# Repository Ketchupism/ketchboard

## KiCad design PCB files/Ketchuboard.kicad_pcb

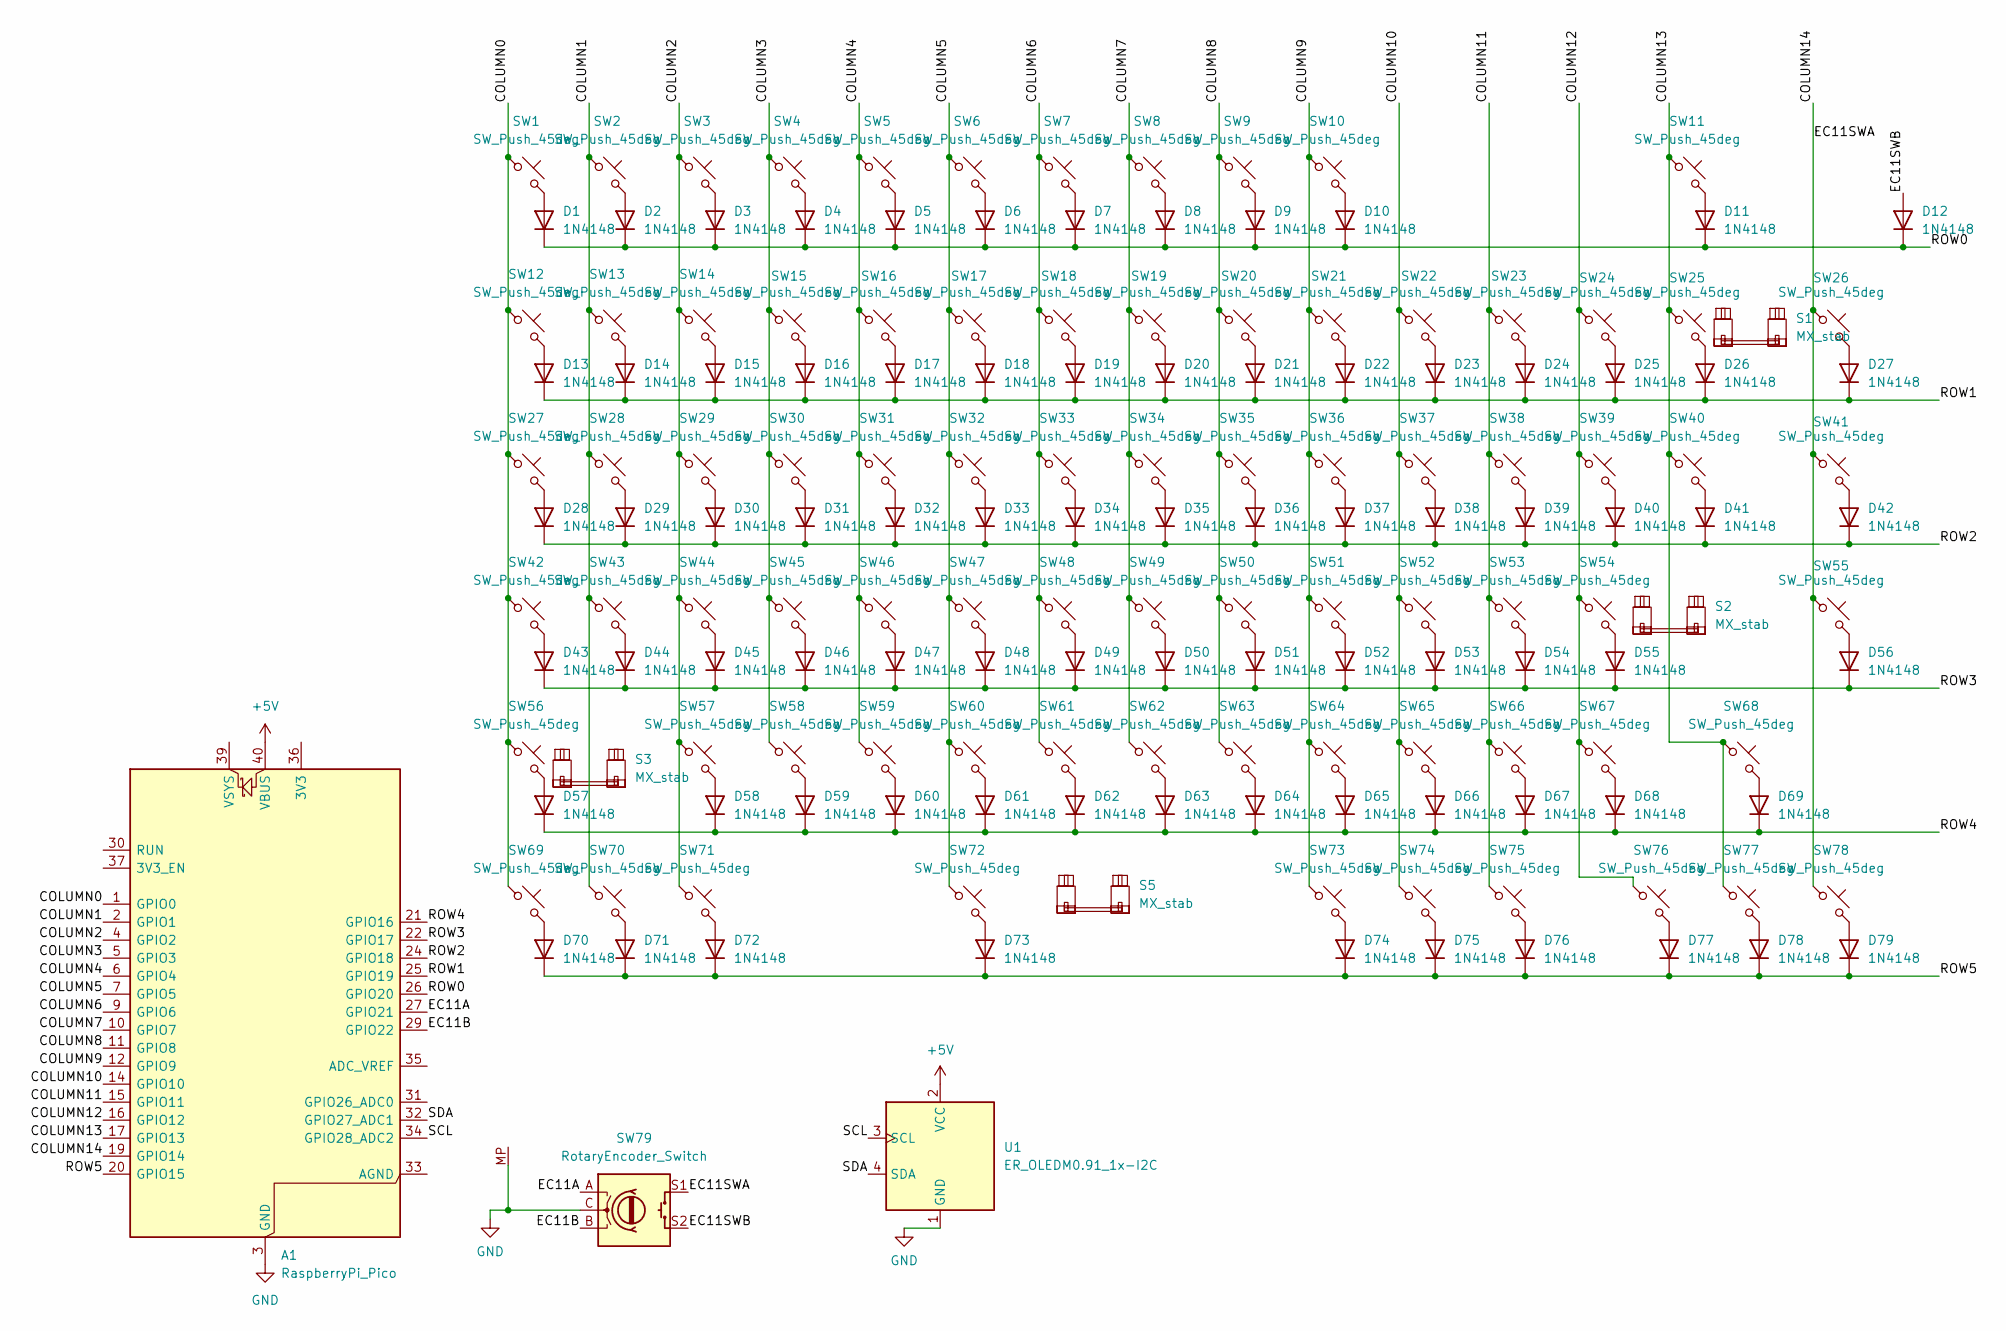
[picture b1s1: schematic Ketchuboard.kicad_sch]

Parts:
A1: RaspberryPi_Pico; RaspberryPi_Pico_Common_THT
D1, D2, D3, D4, D5, D6, D7, D8, D9, D10, D11, D12, D13, D14, D15, D16, D17, D18, D19, D20, D21, D22, D23, D24, D25, D26, D27, D28, D29, D30, D31, D32, D33, D34, D35, D36, D37, D38, D39, D40, D41, D42, D43, D44, D45, D46, D47, D48, D49, D50, D51, D52, D53, D54, D55, D56, D57, D58, D59, D60, D61, D62, D63, D64, D65, D66, D67, D68, D69, D70, D71, D72, D73, D74, D75, D76, D77, D78, D79: 1N4148; D_DO-35_SOD27_P7.62mm_Horizontal
S1: MX_stab; STAB_MX_6.25u
S2, S3: MX_stab; STAB_MX_2.25u
S5: MX_stab; STAB_MX_2u
SW1, SW2, SW3, SW4, SW5, SW6, SW7, SW8, SW9, SW10, SW11, SW12, SW13, SW14, SW15, SW16, SW17, SW18, SW19, SW20, SW21, SW22, SW23, SW24, SW25, SW26, SW28, SW29, SW30, SW31, SW32, SW33, SW34, SW35, SW36, SW37, SW38, SW39, SW41, SW43, SW44, SW45, SW46, SW47, SW48, SW49, SW50, SW51, SW52, SW53, SW54, SW55, SW56, SW57, SW58, SW59, SW60, SW61, SW62, SW63, SW64, SW65, SW66, SW68, SW72, SW73, SW74, SW75, SW76, SW77, SW78: SW_Push_45deg; SW_MX_1u
SW27, SW40: SW_Push_45deg; SW_MX_1.5u
SW42, SW67: SW_Push_45deg; SW_MX_1.75u
SW69, SW70, SW71: SW_Push_45deg; SW_MX_1.25u
SW79: RotaryEncoder_Switch; ROT_Alps_EC11E-Switch
U1: ER_OLEDM0.91_1x-I2C

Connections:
+5V: A1.40 (VBUS), U1.2 (VCC)
/COLUMN0: A1.1 (GPIO0), SW1.1, SW12.1, SW27.1, SW42.1, SW56.1, SW69.1
/COLUMN1: A1.2 (GPIO1), SW2.1, SW13.1, SW28.1, SW43.1, SW70.1
/COLUMN2: A1.4 (GPIO2), SW3.1, SW14.1, SW29.1, SW44.1, SW57.1, SW71.1
/COLUMN3: A1.5 (GPIO3), SW4.1, SW15.1, SW30.1, SW45.1, SW58.1
/COLUMN4: A1.6 (GPIO4), SW5.1, SW16.1, SW31.1, SW46.1, SW59.1
/COLUMN5: A1.7 (GPIO5), SW6.1, SW17.1, SW32.1, SW47.1, SW60.1, SW72.1
/COLUMN6: A1.9 (GPIO6), SW7.1, SW18.1, SW33.1, SW48.1, SW61.1
/COLUMN7: A1.10 (GPIO7), SW8.1, SW19.1, SW34.1, SW49.1, SW62.1
/COLUMN8: A1.11 (GPIO8), SW9.1, SW20.1, SW35.1, SW50.1, SW63.1
/COLUMN9: A1.12 (GPIO9), SW10.1, SW21.1, SW36.1, SW51.1, SW64.1, SW73.1
/COLUMN10: A1.14 (GPIO10), SW22.1, SW37.1, SW52.1, SW65.1, SW74.1
/COLUMN11: A1.15 (GPIO11), SW23.1, SW38.1, SW53.1, SW66.1, SW75.1
/COLUMN12: A1.16 (GPIO12), SW24.1, SW39.1, SW54.1, SW67.1, SW76.1
/COLUMN13: A1.17 (GPIO13), SW11.1, SW25.1, SW40.1, SW68.1, SW77.1
/COLUMN14: A1.19 (GPIO14), SW26.1, SW41.1, SW55.1, SW78.1, SW79.S1
/EC11A: A1.27 (GPIO21), SW79.A
/EC11B: A1.29 (GPIO22), SW79.B
/EC11SWB: D12.2 (A), SW79.S2
/ROW0: A1.26 (GPIO20), D1.1 (K), D2.1 (K), D3.1 (K), D4.1 (K), D5.1 (K), D6.1 (K), D7.1 (K), D8.1 (K), D9.1 (K), D10.1 (K), D11.1 (K), D12.1 (K)
/ROW1: A1.25 (GPIO19), D13.1 (K), D14.1 (K), D15.1 (K), D16.1 (K), D17.1 (K), D18.1 (K), D19.1 (K), D20.1 (K), D21.1 (K), D22.1 (K), D23.1 (K), D24.1 (K), D25.1 (K), D26.1 (K), D27.1 (K)
/ROW2: A1.24 (GPIO18), D28.1 (K), D29.1 (K), D30.1 (K), D31.1 (K), D32.1 (K), D33.1 (K), D34.1 (K), D35.1 (K), D36.1 (K), D37.1 (K), D38.1 (K), D39.1 (K), D40.1 (K), D41.1 (K), D42.1 (K)
/ROW3: A1.22 (GPIO17), D43.1 (K), D44.1 (K), D45.1 (K), D46.1 (K), D47.1 (K), D48.1 (K), D49.1 (K), D50.1 (K), D51.1 (K), D52.1 (K), D53.1 (K), D54.1 (K), D55.1 (K), D56.1 (K)
/ROW4: A1.21 (GPIO16), D57.1 (K), D58.1 (K), D59.1 (K), D60.1 (K), D61.1 (K), D62.1 (K), D63.1 (K), D64.1 (K), D65.1 (K), D66.1 (K), D67.1 (K), D68.1 (K), D69.1 (K)
/ROW5: A1.20 (GPIO15), D70.1 (K), D71.1 (K), D72.1 (K), D73.1 (K), D74.1 (K), D75.1 (K), D76.1 (K), D77.1 (K), D78.1 (K), D79.1 (K)
/SCL: A1.34 (GPIO28_ADC2), U1.3 (SCL)
/SDA: A1.32 (GPIO27_ADC1), U1.4 (SDA)
GND: A1.3 (GND), A1.8 (GND), A1.13 (GND), A1.18 (GND), A1.23 (GND), A1.28 (GND), A1.38 (GND), SW79.C, SW79.MP, U1.1 (GND)
unnamed: D1.2 (A), SW1.2
unnamed: D2.2 (A), SW2.2
unnamed: D3.2 (A), SW3.2
unnamed: D4.2 (A), SW4.2
unnamed: D5.2 (A), SW5.2
unnamed: D6.2 (A), SW6.2
unnamed: D7.2 (A), SW7.2
unnamed: D8.2 (A), SW8.2
unnamed: D9.2 (A), SW9.2
unnamed: D10.2 (A), SW10.2
unnamed: D11.2 (A), SW11.2
unnamed: D13.2 (A), SW12.2
unnamed: D14.2 (A), SW13.2
unnamed: D15.2 (A), SW14.2
unnamed: D16.2 (A), SW15.2
unnamed: D17.2 (A), SW16.2
unnamed: D18.2 (A), SW17.2
unnamed: D19.2 (A), SW18.2
unnamed: D20.2 (A), SW19.2
unnamed: D21.2 (A), SW20.2
unnamed: D22.2 (A), SW21.2
unnamed: D23.2 (A), SW22.2
unnamed: D24.2 (A), SW23.2
unnamed: D25.2 (A), SW24.2
unnamed: D26.2 (A), SW25.2
unnamed: D27.2 (A), SW26.2
unnamed: D28.2 (A), SW27.2
unnamed: D29.2 (A), SW28.2
unnamed: D30.2 (A), SW29.2
unnamed: D31.2 (A), SW30.2
unnamed: D32.2 (A), SW31.2
unnamed: D33.2 (A), SW32.2
unnamed: D34.2 (A), SW33.2
unnamed: D35.2 (A), SW34.2
unnamed: D36.2 (A), SW35.2
unnamed: D37.2 (A), SW36.2
unnamed: D38.2 (A), SW37.2
unnamed: D39.2 (A), SW38.2
unnamed: D40.2 (A), SW39.2
unnamed: D41.2 (A), SW40.2
unnamed: D42.2 (A), SW41.2
unnamed: D43.2 (A), SW42.2
unnamed: D44.2 (A), SW43.2
unnamed: D45.2 (A), SW44.2
unnamed: D46.2 (A), SW45.2
unnamed: D47.2 (A), SW46.2
unnamed: D48.2 (A), SW47.2
unnamed: D49.2 (A), SW48.2
unnamed: D50.2 (A), SW49.2
unnamed: D51.2 (A), SW50.2
unnamed: D52.2 (A), SW51.2
unnamed: D53.2 (A), SW52.2
unnamed: D54.2 (A), SW53.2
unnamed: D55.2 (A), SW54.2
unnamed: D56.2 (A), SW55.2
unnamed: D57.2 (A), SW56.2
unnamed: D58.2 (A), SW57.2
unnamed: D59.2 (A), SW58.2
unnamed: D60.2 (A), SW59.2
unnamed: D61.2 (A), SW60.2
unnamed: D62.2 (A), SW61.2
unnamed: D63.2 (A), SW62.2
unnamed: D64.2 (A), SW63.2
unnamed: D65.2 (A), SW64.2
unnamed: D66.2 (A), SW65.2
unnamed: D67.2 (A), SW66.2
unnamed: D68.2 (A), SW67.2
unnamed: D69.2 (A), SW68.2
unnamed: D70.2 (A), SW69.2
unnamed: D71.2 (A), SW70.2
unnamed: D72.2 (A), SW71.2
unnamed: D73.2 (A), SW72.2
unnamed: D74.2 (A), SW73.2
unnamed: D75.2 (A), SW74.2
unnamed: D76.2 (A), SW75.2
unnamed: D77.2 (A), SW76.2
unnamed: D78.2 (A), SW77.2
unnamed: D79.2 (A), SW78.2

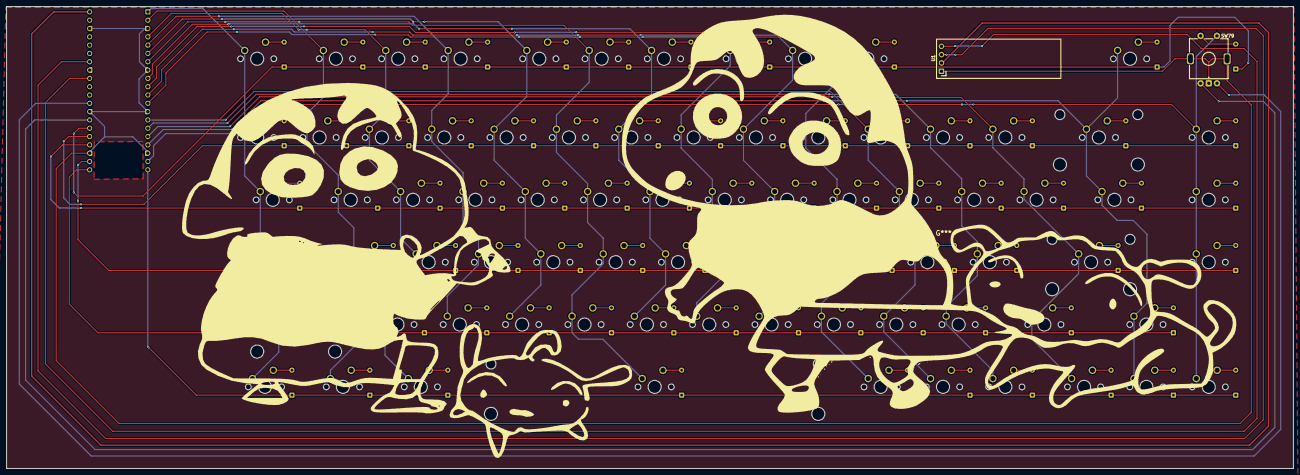
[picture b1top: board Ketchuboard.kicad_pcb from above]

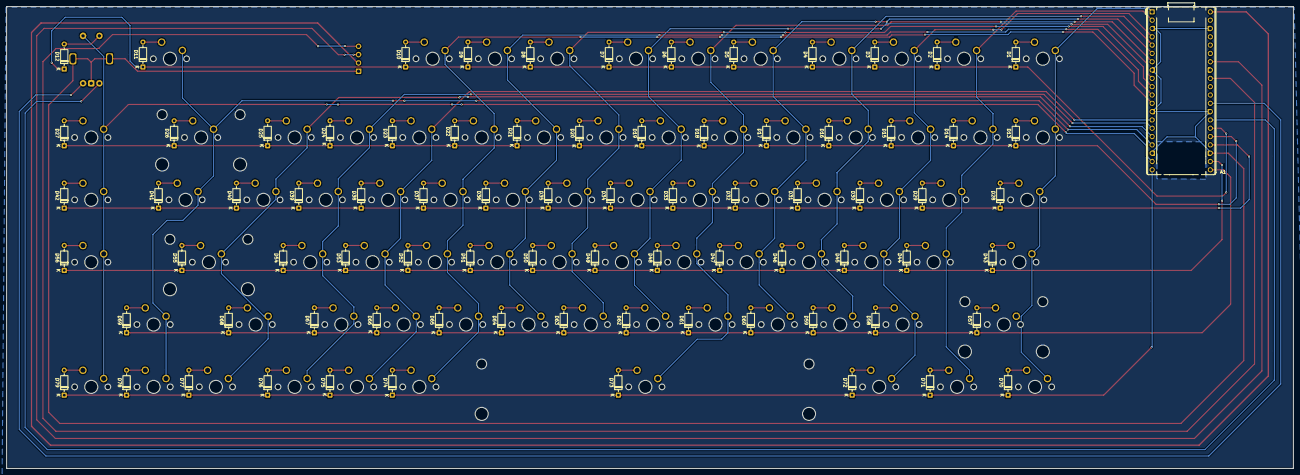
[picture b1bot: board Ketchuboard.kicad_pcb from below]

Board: 2 copper layers, 393.2 x 141.1 mm, 164 parts (80 on the bottom side), 106 nets.
